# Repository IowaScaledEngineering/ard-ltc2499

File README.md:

# Iowa Scaled Engineering ARD-LTC2499

## Summary

The [ARD-LTC2499](https://www.iascaled.com/store/ARD-LTC2499) is an Arduino-compatible shield that contains a Linear Technology LTC2499 24-bit ADC
coupled with an LT6654 precision voltage reference. It is capable of converting 16 single-ended channels,
8 differential channels, or any other combination. In addition to measuring voltage, the ADC can interface
directly to a variety of sensors including strain gauges, thermocouples, and current shunts. The onboard EEPROM
can be used to store calibration and configuration information directly on each ARD-LTC2499 board.
A 6-byte EUI-48-compatible globally unique ID number is also provided.  The ARD-LTC2499 can be used with other
Arduino shields to make a simple, yet very accurate, data acquisition system.

Note:  The normal ARD-LTC2499 is not compatible with Arduinos using 3.3V I/O on the I2C lines, such as the Due, Zero, etc.
This is because the LTC2499 requires a 5V supply to deal with the 4.096V reference voltage, making it incompatible with 3.3V I2C.
A 3.3V compatible version is [available as the ARD-LTC2499-3V3](https://www.iascaled.com/store/ARD-LTC2499-3V3), which
is identical except that it also includes on-board level shifters for the I2C lines.

### Features

* Precision 24-bit delta sigma ADC in an Arduino-friendly form factor
* 16 single-ended channels, 8 differential channels, or any combination
* 7.5 samples/sec (or 15 samples/second without automatic offset cancellation)
* Input common mode voltage range of -0.3V to 5.3V
* Input measurement range of 0-2.048V (single-ended) or -2.048V to 2.048V (differential)
* 4.096V LT6654 precision voltage reference on board
* Optional onboard 5V linear regulator provides clean power to the ADC and reference
* 128 bytes of onboard EEPROM for storing configuration or calibration values
* Read-only 6-byte EUI-48-compatible globally unique ID
* Arduino software library for easy use
* 5V compatible I2C interface (or 3.3-5V with the ARD-LTC2499-3V3)

## Operation of the ARD-LTC2499 Hardware

The latest schematics for both the ARD-LTC2499 and the ARD-LTC2499-3V3 can be found here:
* [ARD-LTC2499 v1.3](https://github.com/IowaScaledEngineering/ard-ltc2499/raw/master/pg/ard-ltc2499-v1.3-83eb2df/ard-ltc2499.pdf)
* [ARD-LTC2499-3V3 v1.3](https://github.com/IowaScaledEngineering/ard-ltc2499/raw/master/pg/ard-ltc2499-v1.3LS-ffd4822/ard-ltc2499.pdf)

The Golden Rule:  When in doubt, check [the LTC2499
datasheet](https://www.analog.com/media/en/technical-documentation/data-sheets/2499fe.pdf).  This guide is not
designed to be a comprehensive guide to the LTC2499.

The useful measuring range of the inputs is 0V to 2.048V in single-ended mode, and a +/-2.048V in differential mode.
Be careful of common mode limits, however. Inputs have an absolute maximum common mode limit of -0.3V to +0.3V above VCC (nominally 5V)
before damage to the part will occur, so while the differential inputs can have -2.048V between them, neither side of the input may
violate the limit of -0.3V to 5.3V without damaging the part.

To eliminate any possibility of introducing gain or offset errors from buffering, the pins of the LTC2499 are brought directly
to the terminal headers. Please be careful when handling and using the board. Errant electrostatic discharge or voltages applied
outside the absolute maximum limits specified in the datasheet can cause immediate damage.

The 4.096V Reference output on J3 comes directly from the LT6654 reference output with no buffering. The LT6654 is rated for a
maximum of +/- 10mA. Also note that any current drawn from this pin will degrade the accuracy of the reference by a
small amount (see the Electrical Characteristics table, "Load Regulation", in the LT6654 datasheet).

### Hardware Configuration

In order to adapt to a wide variety of use cases and ArduinoTM configurations, the ARD-LTC2499 board has a number of configuration jumpers.

* JP1 - I2C Pull-up Enable
* JP2 - I2C Pin Selection
* JP3 - Onboard 5V Linear Regulator Enable
* JP4, JP5 & JP6 - LTC2499 I2C Address
* JP7 & JP8 - EEPROM I2C Address

_JP1 - I2C Pull-up Enable_

The I2C bus depends upon a set of pull-up resistors to function correctly. Each I2C bus should have one and only one set of
pull-ups enabled. The ARD-LTC2499 includes a set of 1.6k pull-up resistors that can be enabled by jumpering pins 1-2 and pins 3-4 of JP1.
Note that Arduino boards do not typically provide I2C pull-ups, so at least one board connected to I2C must provide them.

_JP2 - I2C Pin Selection_

Not all Arduinos provide I2C on the same pins. With the Rev 3 hardware designs (almost all of them as of 2021), there are now a
dedicated set of pins above AREF and GND marked "SDA" and "SCL". If you see those on your board, then place jumpers between
pins 3-5 and 4-6 on JP2 to connect the I2C bus to them.

If you board does not have explicit SDA and SCL pins, then most likely they're shared with pins A4 and A5. Place jumpers
between pins 1-3 and 2-4 to select those instead.

_JP3 - Onboard 5V Linear Regulator Enable_

To free the LTC2499 from any noise on the Arduino's 5V supply caused by the AVR or other shields, the ARD-LTC2499 includes an
onboard 78L05 regulator coming from the Arduino's "VIN" pin. If you are powering the Arduino with >8VDC via the power jack,
you can use the ARD-LTC2499 onboard 5V regulator to provide nice quiet power by jumpering pins 3-4 of JP3.

If you are powering the Arduino off of the 5V provided by USB or via some other means that does not place >8VDC on the VIN pin,
then the regulator will not work and must not be used. JP3 must be placed between pins 1-2 in this case.

_JP4, JP5 & JP6 - LTC2499 I2C Address_

Each device on the I2C bus must have a unique device address. The LTC2499 has 27 possible addresses depending on how
JP4, JP5, and JP6 are set. Each may be set high (jumpering pins 1-2, the two closest to the LTC2499), low (jumpering pins 3-4,
the ones furthest from the 2499) or floating (no jumpered pins or pins 2-3 jumpered).  JP4 corresponds to CA0, JP5 to CA1, and JP6 to CA2 on the LTC2499.

| JP4    | JP5    | JP6    | 7-bit I2C Address | Ard2499 Define       |
|--------|--------|--------|-------------------|----------------------|
| Low    | Low    | Low    | 0x14              | ARD2499_ADC_ADDR_000 |
| Low    | Low    | Open   | 0x15              | ARD2499_ADC_ADDR_00Z |
| Low    | Low    | High   | 0x16              | ARD2499_ADC_ADDR_001 |
| Low    | Open   | Low    | 0x17              | ARD2499_ADC_ADDR_0Z0 |
| Low    | Open   | Open   | 0x24              | ARD2499_ADC_ADDR_0ZZ |
| Low    | Open   | High   | 0x25              | ARD2499_ADC_ADDR_0Z1 |
| Low    | High   | Low    | 0x26              | ARD2499_ADC_ADDR_010 |
| Low    | High   | Open   | 0x27              | ARD2499_ADC_ADDR_01Z |
| Low    | High   | High   | 0x28              | ARD2499_ADC_ADDR_011 |
| Open   | Low    | Low    | 0x35              | ARD2499_ADC_ADDR_Z00 |
| Open   | Low    | Open   | 0x36              | ARD2499_ADC_ADDR_Z0Z |
| Open   | Low    | High   | 0x37              | ARD2499_ADC_ADDR_Z01 |
| Open   | Open   | Low    | 0x44              | ARD2499_ADC_ADDR_ZZ0 |
| Open   | Open   | Open   | 0x45              | ARD2499_ADC_ADDR_ZZZ |
| Open   | Open   | High   | 0x46              | ARD2499_ADC_ADDR_ZZ1 |
| Open   | High   | Low    | 0x47              | ARD2499_ADC_ADDR_Z10 |
| Open   | High   | Open   | 0x54              | ARD2499_ADC_ADDR_Z1Z |
| Open   | High   | High   | 0x55              | ARD2499_ADC_ADDR_Z11 |
| High   | Low    | Low    | 0x56              | ARD2499_ADC_ADDR_100 |
| High   | Low    | Open   | 0x57              | ARD2499_ADC_ADDR_10Z |
| High   | Low    | High   | 0x64              | ARD2499_ADC_ADDR_101 |
| High   | Open   | Low    | 0x65              | ARD2499_ADC_ADDR_1Z0 |
| High   | Open   | Open   | 0x66              | ARD2499_ADC_ADDR_1ZZ |
| High   | Open   | High   | 0x67              | ARD2499_ADC_ADDR_1Z1 |
| High   | High   | Low    | 0x74              | ARD2499_ADC_ADDR_110 |
| High   | High   | Open   | 0x75              | ARD2499_ADC_ADDR_11Z |
| High   | High   | High   | 0x76              | ARD2499_ADC_ADDR_111 |

_JP7 & JP8 - EEPROM I2C Address_

Each device on the I2C bus must have a unique device address. The 24AA025E48 EEPROM that provides both non-volatile storage
and the globally unique ID number has four possible addresses depending on how JP7 and JP8 are set. Each may be set high (no jumper)
or low (jumper in place). Please refer to the Figure 5-2 in the 24AA025E48 datasheet (we use the SOT-23 version, so A2 is always '0' -
otherwise JP8 is A1 and JP7 is A0) or the Ard2499 library header for corresponding address values.

| JP7    | JP8    | 7-bit I2C Address | Ard2499 Define      |
|--------|--------|-------------------|---------------------|
| Jumper | Jumper | 0x50              | ARD2499_EEP_ADDR_00 |
| Jumper | Open   | 0x51              | ARD2499_EEP_ADDR_0Z |
| Open   | Jumper | 0x52              | ARD2499_EEP_ADDR_Z0 |
| Open   | Open   | 0x53              | ARD2499_EEP_ADDR_ZZ |

## Ard2499 Arduino Software Library

### Introduction

The Ard2499 library was designed to make the Iowa Scaled Engineering ARD-LTC2499 shield easy to use with the Arduino environment.
The board itself is provides a breakout for the Linear Technology LTC2499 24-bit 8/16 channel delta-sigma ADC, adding other useful
features like a precision 4.096V LT6654 reference, 128 bytes of onboard EEPROM for storing configuration or calibration values,
and a read-only 6-byte EUI48-compatible globally unique ID number.

Note:  The software library is now maintained in [its own repository](https://github.com/IowaScaledEngineering/arduino-ard2499) for compatibility
with Arduino's Library Manager.

### Setup

There are two ways to install the Ard2499 library in the Arduino environment.

The easiest way is through Arduino's Library Manager.  You should be able to search for Ard2499 and have the library available for installation shortly.
We're working on it.

Alternately, you can [download the zip file](https://github.com/IowaScaledEngineering/arduino-ard2499/archive/main.zip) from the
IowaScaledEngineering/arduino-ard2499 project on Github and follow the ["Importing a .zip Library" instructions](https://www.arduino.cc/en/guide/libraries#toc4).

### Example Sketch

Once the library is installed, you should see Ard2499 under File->Examples in your Arduino environment.  A sample Arduino sketch that demonstrates some
simple uses of the library is available as ard2499_example directory.

### Library Usage Details

The core of the Ard2499 library is the Ard2499 object.  One instance should be instantiated for each ARD-LTC2499 board that you are using.

When an instance is created, an optional TwoWire object can be passed to the constructor.  Otherwise, the Ard2499 library assumes that the board will be communicating using the Wire object.

#### Functional Interface

```byte Ard2499::begin(byte ltc2499Address, byte eepromAddress, uint16_t referenceMillivolts = 4096);```

The Ard2499::begin() function should be called within the setup() function of your sketch. It requires the 7-bit address of both the LTC2499 and EEPROM on the ARD-LTC2499 to initialize both parts.
The addresses can be passed in directly as a number, or by using the address macros.  By using different addresses, it's possible to stack ARD-LTC2499 boards and have a different object to control each one.

An optional reference voltage, in millivolts, can be passed if the ARD-LTC2499 has a non-standard reference on board. If not specified, it defaults to 4096mV, which is the voltage
for any non-special order board.

Returns:  Ard2499::begin() will return a byte corresponding to a bitmast of errors, with 0 corresponding to complete success.
* ARD2499_SUCCESS (0x00) upon both devices being initialized successfully
* ARD2499_LTC2499_ERR (0x01) if the LTC2499 is not initialized successfully
* ARD2499_EEPROM_ERR (0x02) if the EEPROM is not initialized successfully

```byte Ard2499::ltc2499ChangeChannel(byte channel)```

The Ard2499::ltc2499ChangeChannel() function will wait for up to 200 milliseconds for the LTC2499 to become available, change the LTC2499's input multiplexer to the channel
specified in channel and start a new conversion. The value in channel corresponds to the lower 5 bits in the first configuration word of the device. In addition to computing
values for channel yourself, you can use the channel macros.

Additionally, channel can be configured to LTC2499_CHAN_TEMPERATURE to return the LTC2499 internal temperature. While the temperature input isn't a "channel" on the multiplexer,
the library makes it appear this way.

Returns:
* ARD2499_SUCCESS (0x00) if the channel change completed
* ARD2499_LTC2499_ERR (0x02) if the channel change failed

```byte Ard2499::ltc2499ChangeConfiguration(byte config)```

The Ard2499::ltc2499ChangeConfiguration() function will wait for up to 200 milliseconds for the LTC2499 to become available, change the LTC2499's configuration to that
specified in config and start a new conversion. The value in config corresponds to bits 3-5 in the second configuration word of the device. In addition to computing values
for config yourself, you can use the configuration macros.

Returns:
* ARD2499_SUCCESS (0x00) if the configuration change completed
* ARD2499_LTC2499_ERR (0x02) if the configuration change failed

```long Ard2499:: ltc2499Read()```

The Ard2499::ltc2499Read() function will wait for up to 200 milliseconds for the LTC2499 to become available, read the last conversion value, start a new conversion,
and clean up the conversion result.

Returns:
* -16777216 to +16777215 - normal conversion result
* LTC2499_READ_ERROR (0x01000001) if the read timed out or otherwise failed
* LTC2499_OVERRANGE_POSITIVE (0x01000000) if (IN+ - IN-) > 2.048V
* LTC2499_OVERRANGE_NEGATIVE (0x11000000) if (IN+ - IN-) < 2.048V

```long Ard2499:: ltc2499ReadAndChangeChannel(byte nextChannel)```

The Ard2499::ltc2499ReadAndChangeChannel() function will first attempt to change the input multiplexer channel and then perform a read. This is useful for not wasting
the conversion (and delay) resulting from a normal Ard2499::ltc2499Read() if the next operation is just going to be changing the input channel. Note: the channel change
does not take effect until after the data is read - in other words, for the next conversion.

Channel change behaviour works exactly like Ard2499::ltc2499ChangeChannel(). In the event that the channel change fails, LTC2499_READ_ERROR will be returned. Otherwise,
read and return behaviour works exactly like Ard2499::ltc2499Read().

```unsigned long Ard2499:: ltc2499ReadRaw()```

The Ard2499::ltc2499ReadRaw() function will wait for up to 200 milliseconds for the LTC2499 to become available, read the last conversion value, start a new conversion,
and return the native 32 bit conversion result. The lowest 6 bits will be "sub-LSB" bits, and the highest bit will be what the datasheet designates "SIG". This is for
advanced users who want direct access to the conversion result.

Returns:
* LTC2499_RAW_READ_ERROR (0xFFFFFFFF) if the read timed out or otherwise failed
* Any other result is a direct read from the LTC2499

```unsigned long Ard2499:: ltc2499ReadRawAndChangeChannel(byte nextChannel)```

The Ard2499::ltc2499ReadRawAndChangeChannel() function will first attempt to change the input multiplexer channel and then perform a raw read. This is useful for
not wasting the conversion (and delay) resulting from a normal Ard2499::ltc2499ReadRaw() if the next operation is just going to be changing the input channel.
Note: the channel change does not take effect until after the data is read - in other words, for the next conversion. The raw read capability is for advanced
users who want direct access to the conversion result.

Channel change behaviour works exactly like Ard2499::ltc2499ChangeChannel(). In the event that the channel change fails, LTC2499_RAW_READ_ERROR will be returned.
Otherwise, read and return behaviour works exactly like Ard2499:: ltc2499ReadRaw().

```unsigned int Ard2499:: ltc2499ReadTemperatureDeciK()```

The Ard2499::ltc2499ReadTemperatureDeciK() function will check if the current channel is LTC2499_CHAN_TEMPERATURE and if not, wait up to 200 milliseconds for
converter availability, change it and start a new conversion. It will then wait for up to 200 milliseconds for the LTC2499 to complete the conversion and turn it
into a unsigned int corresponding to the LTC2499's current temperature in 1/10th degrees Kelvin.

Upon failure, it will return zero, as hopefully no project you're working on is operating at absolute zero. If it is and the part still seems to be working
otherwise, call us and we'll help you write the paper for your physics journal of choice.

```float ltc2499ReadTemperature(byte temperatureUnits)```

The Ard2499::ltc2499ReadTemperature() function will check if the current channel is LTC2499_CHAN_TEMPERATURE and if not, wait up to 200 milliseconds for converter
availability, change it and start a new conversion. It will then wait for up to 200 milliseconds for the LTC2499 to complete the conversion and turn it into single
precision floating point value corresponding to the LTC2499's current temperature in the units specified in temperatureUnits.

Upon failure, it will return zero.

The value of temperatureUnits should be ARD2499_TEMP_K (degrees Kelvin), ARD2499_TEMP_C (degrees Celsius), or ARD2499_TEMP_F (degrees Fahrenheit).

Note: Because this function uses floating point on an 8 bit processor without any sort of hardware floating point support, expect performance to be abysmal on
AVR-based Arduinos. But it's handy if you don't care about performance.

```const char* Ard2499::eui48Get()```

The Ard2499::eui48Get() function will retrieve the board's 48-bit, globally unique, EUI-48TM-compatible identification number as a string.

Returns:

Ard2499::eui48Get() will return a character pointer to a constant, NULL-terminated string. The value will be either 12 characters of hexadecimal number,
or "Unknown" if the Ard2499::begin() failed to find the EEPROM. (Ard2499::begin() would have returned a value with the ARD2499_EEPROM_ERR bit set.)

```byte Ard2499::eepromRead(int address, byte defaultOnError=0x00)```

The Ard2499::eepromRead() function will retrieve a byte from the ARD-LTC2499's onboard EEPROM at the location specified by address. Valid values for address are 0x00-0x7F.

Optionally, the function can take a second argument - defaultOnError - of the value to be returned if the EEPROM is not initialized or is not accessible when the function
is called. If the defaultOnError parameter is omitted, it will default to returning 0x00 on failure.

```byte Ard2499::eepromWrite(int address, byte value, byte blocking=1)```

The Ard2499::eepromWrite() function will write a byte of value value to the ARD-LTC2499's onboard EEPROM at the location specified by address. Valid values for address are
0x00-0x7F, and value can be 0x00-0xFF.

Optionally, the function can take a third argument - blocking. The Microchip 24AA025E48 EEPROM used on the ARD-LTC2499 can take up to 5 milliseconds to actually commit
a write to EEPROM. If blocking is non-zero or omitted, the eepromWrite() function will block until it can confirm that the write is completed or until it times out
after 10 millseconds.

Note that blocking will not cause the value to be verified - it merely causes the function to block until the part begins acknowledging I2C/TWI transactions once
again, indicating that the write cycle is complete.

Returns:
* ARD2499_SUCCESS (0x00) if the write completed
* ARD2499_EEPROM_ERR (0x02) if the write failed

#### LTC2499 Address Defines

The address for the LTC2499 is configurable on the ARD-LTC2499 using jumpers JP4-JP6. You can either use the datasheet and directly enter the LTC2499's address into
the Ard2499::begin() function, or use some convenient macros.

The macros are all in the form of ARD2499_ADC_ADDR_cba, where a, b, and c can take on the value of '0', '1', or 'Z'. Placeholder 'a' represents jumper JP4, 'b' represents JP5,
and 'c' JP6. '0' indicates that the center pin is jumpered to the low pins (towards inputs 8-15 on the board), '1' indicates that it is jumpered to the high pins
(towards the LTC2499 or inputs 0-7), and 'Z' indicates that it's left floating (no jumpers or jumper across pin 2-3).

So, if all three were left open, you'd use ARD2499_ADC_ADDR_ZZZ. Likewise, for JP4 to bottom, JP5 to top, and JP6 open you'd use ARD2499_ADC_ADDR_Z10.

#### EEPROM Address Defines

The address for the EEPROM is configurable on the ARD-LTC2499 using jumpers JP7-JP8. You can either use the datasheet and directly enter the 24AA025E48's address into the
Ard2499::begin() function, or use some convenient macros.

The macros are all in the form of ARD2499_EEP_ADDR_ba, where a and b can take on the value of '0' or 'Z'. Placeholder 'a' represents jumper JP7 and 'b' represents JP8.
'0' indicates that a jumper has been placed across those pins, and 'Z' indicates that it's left floating (no jumper).

So, if both were left open, you'd use ARD2499_EEP_ADDR_ZZ. Likewise, for JP7 jumpered and JP8 open ARD2499_EEP_ADDR_Z0.

#### Channel Defines

The library provides definitions of all the common channel combinations to allow the easy selection of input channels without knowing all the internal LTC2499 bits to set.

Differential configurations take the form LTC2499_CHAN_DIFF_aP_bN, where 'a' represents the channel number of the positive input (IN+ in the LTC2499 datasheet)
and 'b' represents the channel number of the negative input (IN-).

Single-ended configurations are in the form LTC2499_CHAN_SINGLE_aP, where again 'a' represents the channel number of the positive (IN+) input.

Additionally, the internal temperature sensor can be selected by using LTC2499_CHAN_TEMPERATURE.

Some examples:
* LTC2499_CHAN_DIFF_2P_3N - Differential, input 2 is IN+, input 3 is IN-
* LTC2499_CHAN_DIFF_11P_10N - Differential, input 11 is IN+, input 10 is IN-
* LTC2499_CHAN_SINGLE_2P - Single ended, input 2 as IN+
* LTC2499_CHAN_SINGLE_10P - Single ended, input 10 as IN+
* LTC2499_CHAN_TEMPERATURE - Connect to internal temperature sensor.

#### Configuration Macros

Bit position macros are provided corresponding to the bits used to define the LTC2499 configuration in the second configuration byte:
* LTC2499_CONFIG2_FA
* LTC2499_CONFIG2_FB
* LTC2499_CONFIG2_SPD

These can be combined into a configuration value by an expression such as:

(_BV(LTC2499_CONFIG2_FA) | _BV(LTC2499_CONFIG2_SPD))

Please see the LTC2499 datasheet, Table 4, to see how these are used directly.

Additionally, the library has some convenient combinations:
* LTC2499_CONFIG2_50HZ_REJ - Reject at 50Hz
* LTC2499_CONFIG2_60HZ_REJ - Reject at 60Hz
* LTC2499_CONFIG2_60_50HZ_REJ - Reject at both 50/60Hz
* LTC2499_CONFIG2_SPEED_2X - Set for double speed conversions, drop offset calibration (15 samples/sec)

To use these, pick one of the rejection configurations and - optionally - bitwise or it with the double speed option and pass it to the the ltc2499ChangeConfiguration() function. For example:

```retval = ard2499.ltc2499ChangeConfiguration(LTC2499_CONFIG2_60_50HZ_REJ | LTC2499_CONFIG2_SPEED_2X)```

### A Note About Converter Latency

Important! Note that the LTC2499 will start a conversion whenever it is read (using ltc2499Read() or similar) or whenever the channel
or configuration is changed. Each conversion will take ~133 milliseconds in 1X mode and ~67 milliseconds in 2X mode. During this conversion time,
the LTC2499 will not respond to I2C/TWI requests. Thus, all calls interacting with the LTC2499 implement code to block until a sane timeout is
reached or the part starts responding. Be aware that when you use these functions, your code may hang up for a conversion time.

To minimize the wasted conversions, functions that read the current value and immediately change the channel (without wasting an entire
conversion cycle in between) are provided in addition to the standard read and channel change functions.

### Source Releases

The latest source code is always available from our GitHub [arduino-ard2499 repository](https://github.com/IowaScaledEngineering/arduino-ard2499).  We've broken it out
from the [main hardware project](https://github.com/IowaScaledEngineering/ard-ltc2499) to allow it to be included into Arduino's Library Manager automatically.

## Open Hardware & Software

Like all public Iowa Scaled Engineering designs, the ARD-LTC2499 is both open hardware and open source software.  The hardware is licensed under Creative Commons BY-SA, and the software is GPL v3.

The board was designed using the gEDA suite of tools (gschem, pcb, etc.), and the files are in the sch, sym, and pcb subdirectories.

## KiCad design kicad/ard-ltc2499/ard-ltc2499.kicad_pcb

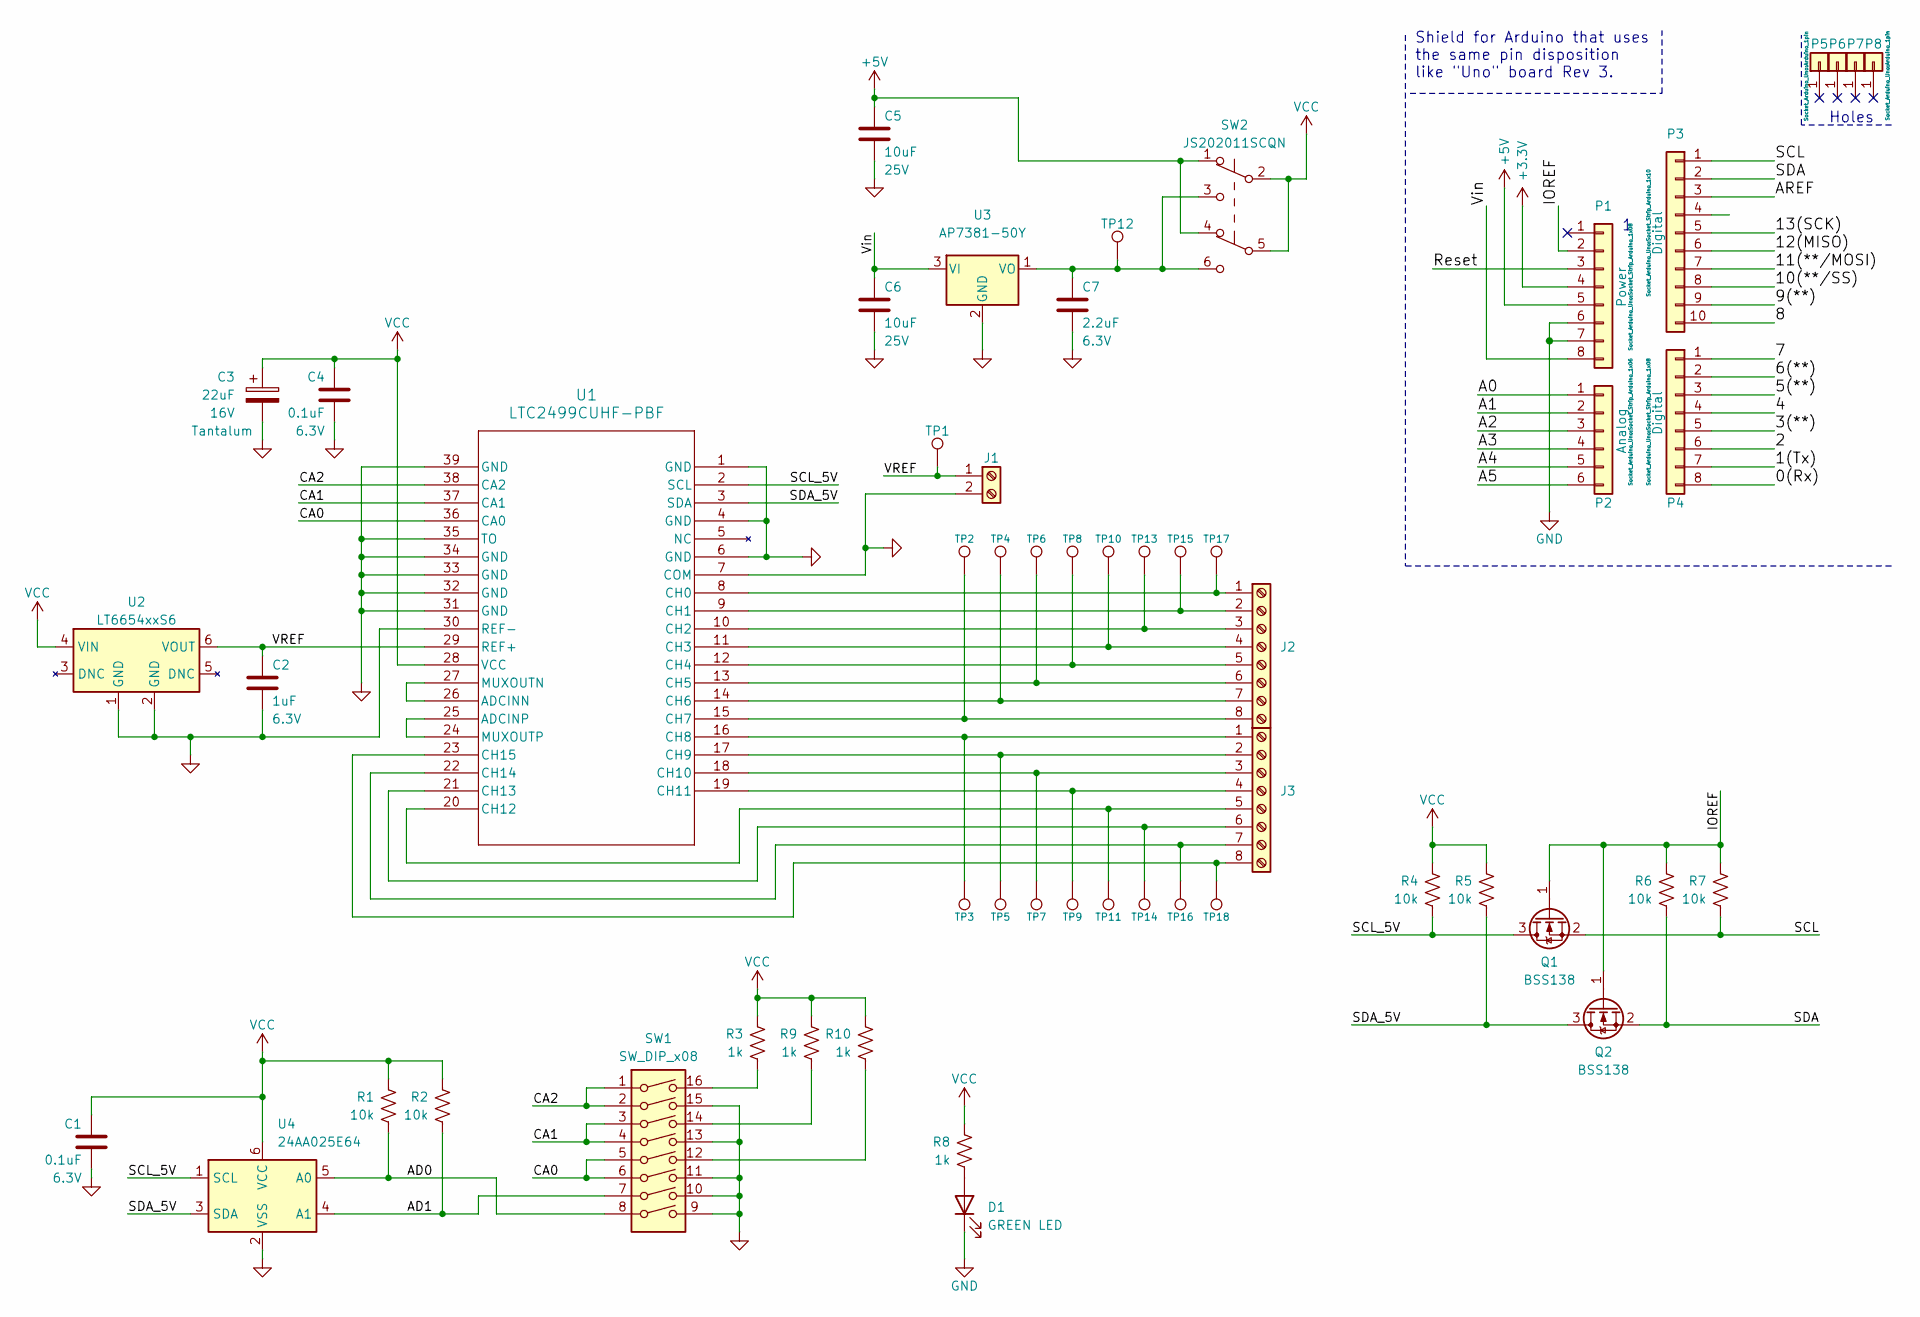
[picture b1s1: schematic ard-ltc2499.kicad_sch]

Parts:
C1, C4: 0.1uF; C_0805_2012Metric; Voltage 6.3V
C2: 1uF; C_0805_2012Metric; Voltage 6.3V
C3: 22uF; CP_EIA-3216-18_Kemet-A; Voltage 16V
C5, C6: 10uF; C_0805_2012Metric; Voltage 25V
C7: 2.2uF; C_0805_2012Metric; Voltage 6.3V
D1: GREEN LED; LED_0805_2012Metric
J1: Screw_Terminal_01x02; TerminalBlock_RND_205-00012_1x02_P5.00mm_Horizontal
J2, J3: Screw_Terminal_01x08; TerminalBlock_TE_282834-8_1x08_P2.54mm_Horizontal
P1: Power; Socket_Strip_Arduino_1x08
P2: Analog; Socket_Strip_Arduino_1x06
P3: Digital; Socket_Strip_Arduino_1x10
P4: Digital; Socket_Strip_Arduino_1x08
P5, P6, P7, P8: CONN_01X01; Arduino_1pin
Q1, Q2: BSS138; SOT-23
R1, R2, R4, R5, R6, R7: 10k; R_0805_2012Metric
R3, R8, R9, R10: 1k; R_0805_2012Metric
SW1: SW_DIP_x08; SW_DIP_SPSTx08_Slide_6.7x21.88mm_W8.61mm_P2.54mm_LowProfile
SW2: JS202011SCQN; SW_JS202011SCQN
TP1, TP2, TP3, TP4, TP5, TP6, TP7, TP8, TP9, TP10, TP11, TP12, TP13, TP14, TP15, TP16, TP17, TP18: TestPoint; TestPoint_Pad_D1.5mm
U1: LTC2499CUHF-PBF; QFN-38_UHF_LIT
U2: LT6654xxS6; TSOT-23-6
U3: AP7381-50Y; SOT-89-3
U4: 24AA025E64; TSOT-23-6

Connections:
+3V3: P1.4
+5V: C5.1, P1.5, SW2.1 (A), SW2.4 (A)
/0(Rx): P4.8
/1(Tx): P4.7
/2: P4.6
/3(**): P4.5
/4: P4.4
/5(**): P4.3
/6(**): P4.2
/7: P4.1
/8: P3.10
/9(**): P3.9
/10(**/SS): P3.8
/11(**/MOSI): P3.7
/12(MISO): P3.6
/13(SCK): P3.5
/A0: P2.1
/A1: P2.2
/A2: P2.3
/A3: P2.4
/A4: P2.5
/A5: P2.6
/AD0: R1.1, SW1.8, U4.5 (A0)
/AD1: R2.1, SW1.7, U4.4 (A1)
/AREF: P3.3
/CA0: SW1.5, SW1.6, U1.36 (CA0)
/CA1: SW1.3, SW1.4, U1.37 (CA1)
/CA2: SW1.1, SW1.2, U1.38 (CA2)
/IOREF: P1.2, Q1.1 (G), Q2.1 (G), R6.2, R7.2
/Reset: P1.3
/SCL: P3.1, Q1.2 (S), R7.1
/SCL_5V: Q1.3 (D), R4.1, U1.2 (SCL), U4.1 (SCL)
/SDA: P3.2, Q2.2 (S), R6.1
/SDA_5V: Q2.3 (D), R5.1, U1.3 (SDA), U4.3 (SDA)
/VREF: C2.1, J1.1, TP1.1, U1.29 (REF+), U2.6 (VOUT)
/Vin: C6.1, P1.8, U3.3 (VI)
GND: C1.2, C2.2, C3.2, C4.2, C5.2, C6.2, C7.2, D1.1 (K), J1.2, P1.6, P1.7, SW1.9, SW1.10, SW1.11, SW1.13, SW1.15, U1.1 (GND), U1.4 (GND), U1.6 (GND), U1.7 (COM), U1.30 (REF-), U1.31 (GND), U1.32 (GND), U1.33 (GND), U1.34 (GND), U1.35 (TO), U1.39 (GND), U2.1 (GND), U2.2 (GND), U3.2 (GND), U4.2 (VSS)
unnamed: C7.1, SW2.3 (C), SW2.6 (C), TP12.1, U3.1 (VO)
unnamed: D1.2 (A), R8.1
unnamed: J2.1, TP17.1, U1.8 (CH0)
unnamed: J2.2, TP15.1, U1.9 (CH1)
unnamed: J2.3, TP13.1, U1.10 (CH2)
unnamed: J2.4, TP10.1, U1.11 (CH3)
unnamed: J2.5, TP8.1, U1.12 (CH4)
unnamed: J2.6, TP6.1, U1.13 (CH5)
unnamed: J2.7, TP4.1, U1.14 (CH6)
unnamed: J2.8, TP2.1, U1.15 (CH7)
unnamed: J3.1, TP3.1, U1.16 (CH8)
unnamed: J3.2, TP5.1, U1.17 (CH9)
unnamed: J3.3, TP7.1, U1.18 (CH10)
unnamed: J3.4, TP9.1, U1.19 (CH11)
unnamed: J3.5, TP11.1, U1.20 (CH12)
unnamed: J3.6, TP14.1, U1.21 (CH13)
unnamed: J3.7, TP16.1, U1.22 (CH14)
unnamed: J3.8, TP18.1, U1.23 (CH15)
unnamed: R3.1, SW1.16
unnamed: R9.1, SW1.14
unnamed: R10.1, SW1.12
unnamed: U1.24 (MUXOUTP), U1.25 (ADCINP)
unnamed: U1.26 (ADCINN), U1.27 (MUXOUTN)
VCC: C1.1, C3.1, C4.1, R1.2, R2.2, R3.2, R4.2, R5.2, R8.2, R9.2, R10.2, SW2.2 (B), SW2.5 (B), U1.28 (VCC), U2.4 (VIN), U4.6 (VCC)

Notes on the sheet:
Holes
Shield for Arduino that uses the same pin disposition like "Uno" board Rev 3.

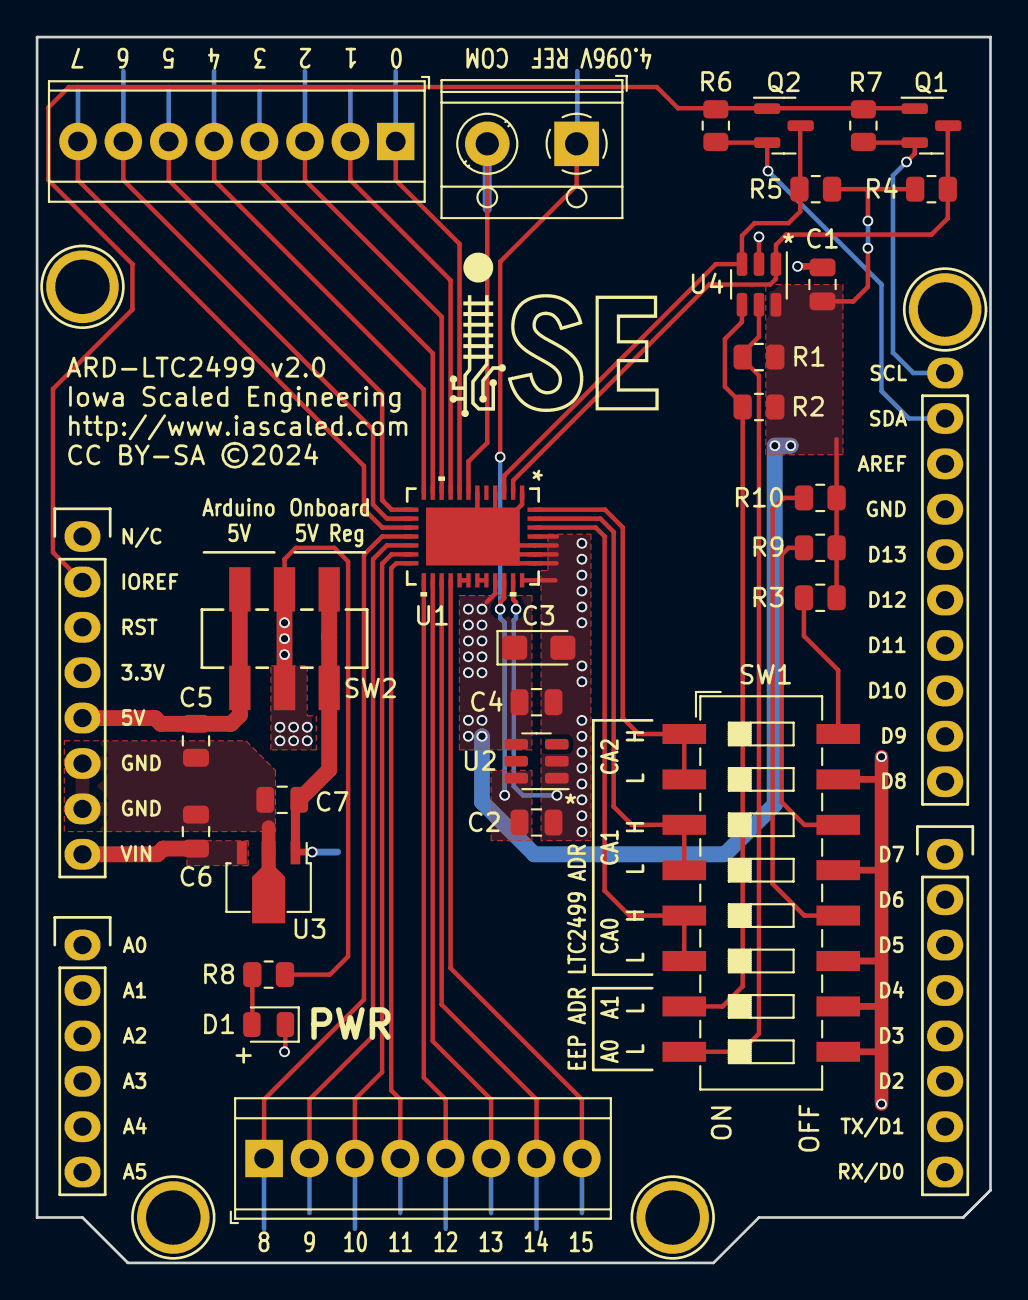
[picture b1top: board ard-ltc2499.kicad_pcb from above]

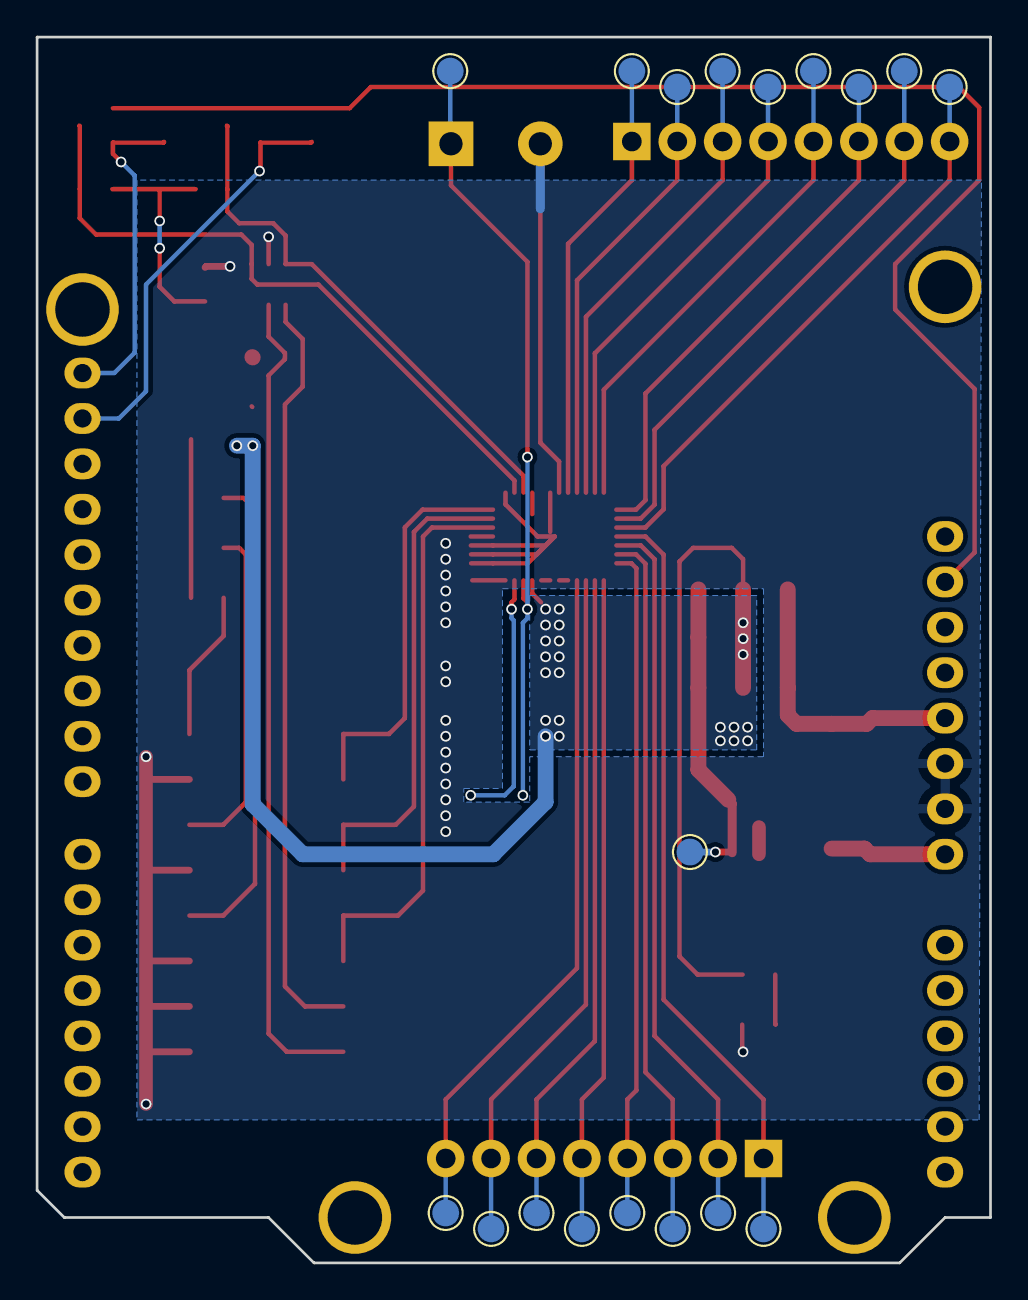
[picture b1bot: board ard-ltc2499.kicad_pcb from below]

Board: 2 copper layers, 53.3 x 68.6 mm, 55 parts (18 on the bottom side), 38 nets.

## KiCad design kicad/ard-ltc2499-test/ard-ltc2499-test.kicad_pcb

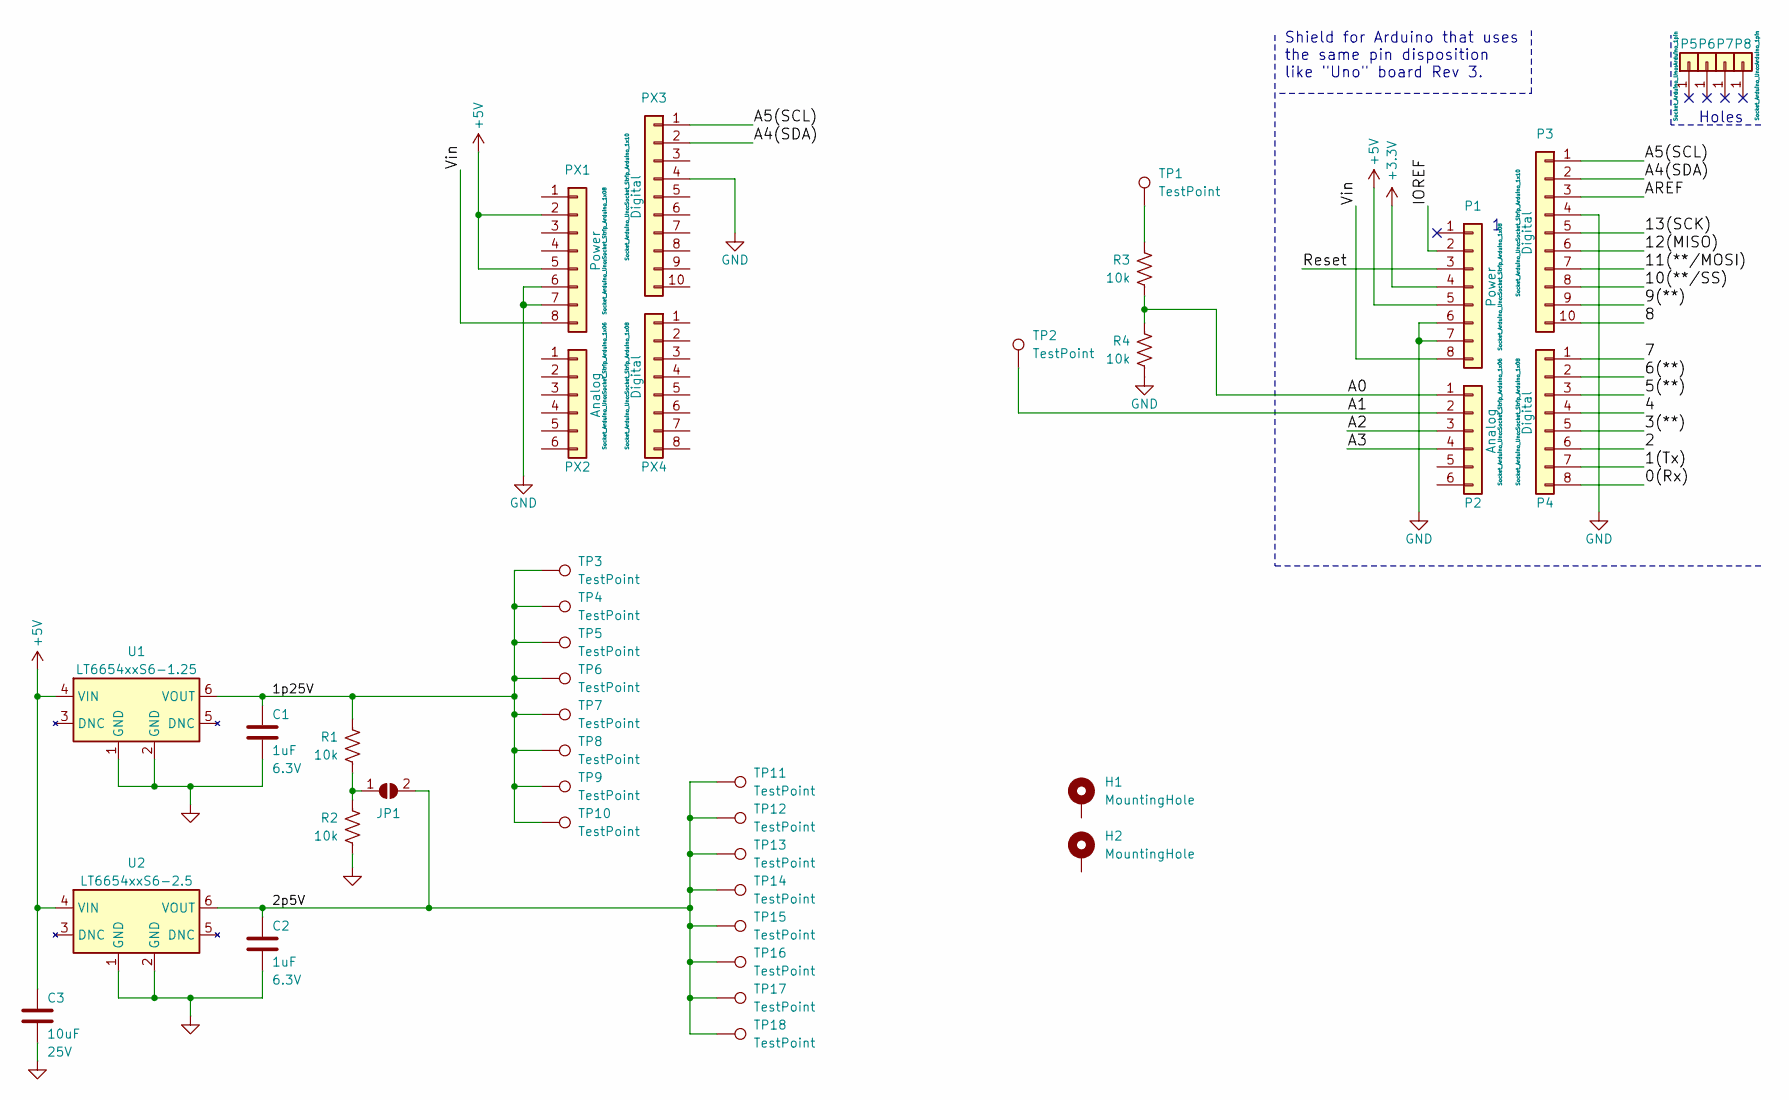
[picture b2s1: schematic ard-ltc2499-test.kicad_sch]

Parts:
C1, C2: 1uF; C_0805_2012Metric; Voltage 6.3V
C3: 10uF; C_0805_2012Metric; Voltage 25V
H1, H2: MountingHole; MountingHole_3.2mm_M3_Pad
JP1: SolderJumper_2_Open; SolderJumper-2_P1.3mm_Open_RoundedPad1.0x1.5mm
P1: Power; Socket_Strip_Arduino_1x08
P2: Analog; Socket_Strip_Arduino_1x06
P3: Digital; Socket_Strip_Arduino_1x10
P4: Digital; Socket_Strip_Arduino_1x08
P5, P6, P7, P8: CONN_01X01; Arduino_1pin
PX1: Power; Socket_Strip_Arduino_1x08
PX2: Analog; Socket_Strip_Arduino_1x06
PX3: Digital; Socket_Strip_Arduino_1x10
PX4: Digital; Socket_Strip_Arduino_1x08
R1, R2, R3, R4: 10k; R_0805_2012Metric
TP1, TP2, TP3, TP4, TP5, TP6, TP7, TP8, TP9, TP10, TP11, TP12, TP13, TP14, TP15, TP16, TP17, TP18: TestPoint; PinHeader_1x01_P2.54mm_Vertical
U1: LT6654xxS6-1.25; TSOT-23-6
U2: LT6654xxS6-2.5; TSOT-23-6

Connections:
+3V3: P1.4
+5V: C3.1, P1.5, PX1.2, PX1.5, U1.4 (VIN), U2.4 (VIN)
/0(Rx): P4.8
/1(Tx): P4.7
/1p25V: C1.1, R1.2, TP3.1, TP4.1, TP5.1, TP6.1, TP7.1, TP8.1, TP9.1, TP10.1, U1.6 (VOUT)
/2: P4.6
/2p5V: C2.1, JP1.2 (B), TP11.1, TP12.1, TP13.1, TP14.1, TP15.1, TP16.1, TP17.1, TP18.1, U2.6 (VOUT)
/3(**): P4.5
/4: P4.4
/5(**): P4.3
/6(**): P4.2
/7: P4.1
/8: P3.10
/9(**): P3.9
/10(**/SS): P3.8
/11(**/MOSI): P3.7
/12(MISO): P3.6
/13(SCK): P3.5
/A0: P2.1, R3.1, R4.2
/A1: P2.2, TP2.1
/A2: P2.3
/A3: P2.4
/A4(SDA): P3.2, PX3.2
/A5(SCL): P3.1, PX3.1
/AREF: P3.3
/IOREF: P1.2
/Reset: P1.3
/Vin: P1.8, PX1.8
GND: C1.2, C2.2, C3.2, P1.6, P1.7, P3.4, PX1.6, PX1.7, PX3.4, R2.1, R4.1, U1.1 (GND), U1.2 (GND), U2.1 (GND), U2.2 (GND)
unnamed: JP1.1 (A), R1.1, R2.2
unnamed: R3.2, TP1.1

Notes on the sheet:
Holes
Shield for Arduino that uses the same pin disposition like "Uno" board Rev 3.

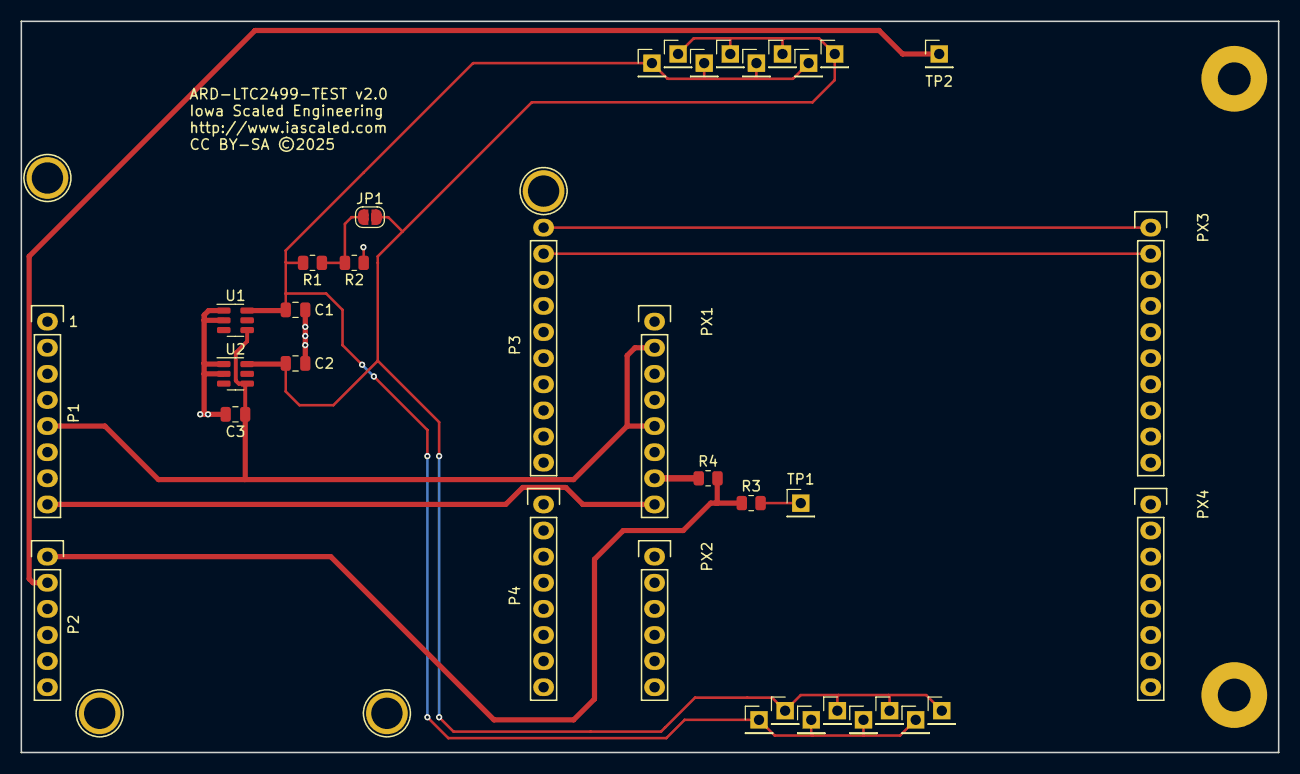
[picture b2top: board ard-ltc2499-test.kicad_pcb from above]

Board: 2 copper layers, 122.3 x 71.1 mm, 42 parts (0 on the bottom side), 11 nets.

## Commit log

2013-01-29 Initial checkin. PCB not complete.
2013-01-30 Finished PCB
2013-01-30 Small cleanup
2013-01-31 Changed C2 to polarized.
2013-01-31 More OCD
2013-01-31 Added polarized cap symbol.
2013-02-01 Added CC license.
2013-02-02 Connected COM to GND. LVS/DRC Clean.
2013-02-03 Add PG files.
2013-03-18 Initial bit of the 2499 arduino library
2013-03-26 This morning's work getting this dumb library to compile and at least eeprom functionality working
2013-03-26 Updates to "mostly working"-ish
2013-03-26 More misc fixes
2013-03-26 Example sketch starting point
2013-03-26 Rename directory to capitalize similar to other Arduino libraries
2013-03-26 Capitalization change
2013-03-27 Renamed the arduino example sketch Fixed a few bugs
2013-03-27 Fixes to add gplv3 boilerplate
2013-03-27 Forgot GPL stuff on arduino sketch
2013-05-02 Added relevant 2499 datasheets
2013-10-12 Added start for HV capable version
2013-10-12 Added thermocouple data
2013-11-25 Fixed LTC6654 to LT6654
2014-03-15 Examples
2014-03-19 Added alarm pin
2014-04-13 Update LTC2499 example code
2014-04-13 Make proper examples directory
2014-04-13 Move of example
2014-04-17 Moved examples to example directory
2014-04-22 Added power LED. Added pin1 marks to U1, U2, U4
2014-04-22 Changed rev to 1.1
2014-04-23 Cleaned up some schtuff.
2014-04-23 Added back silk
2014-04-23 OSHPark order
2014-04-25 Renamed to _reflow (was _thermocouple)
2014-04-27 Latest code with debug pins
2014-05-15 Updated example to enumerate the bus first. Cleaned up reflow example
2014-05-28 Changes to make it more widely arduino compatible
2014-05-28 Changes to example to better describe enumeration and add header text on sketch
2014-10-29 Added test program
2014-10-29 Added extra delay
2014-10-31 Modified to use 4-pin SMT jumpers
2014-10-31 Intermediate layout with SMT jumpers
2014-10-31 Final layout with SMT
2014-11-04 Silk changes to better explain jumpers
2014-11-04 Updated 2499 footprint (smaller paste hole). LVS/DRC clean.
2014-12-01 v1.2
2014-12-07 Fixed LTC2499_CONFIG2_CONFBITS - changed & to |
2014-12-28 Made channel check criteria a range, not just a single-ended comparison
2015-01-09 Create README.md
    Adding readme
2015-01-09 Add license files
2015-01-09 Update readme with more details about the board and ISE
2015-01-18 Modified channel test to check adjacent channel (looking for shorts)
2015-03-08 Verify still connected to original terminal after checking for adjacent.
2015-04-21 Reversed the positive and negative overrange codes in the library. Somehow these have been backwards for years and I've never noticed.
2015-04-24 Added wait for serial after opening port to improve behavior with Leonardo
2015-05-03 Initial commit of volt meter sketch
2015-05-24 Added voltage measurement at end.
2015-07-26 Added note for expected voltage
2015-11-12 Increased annulus around arduino headers (sch/pcb). Changed LED to 0805 (sch only). Changed 2x3 header to SMT (sch only). Replaced R1-R4 with rpack (sch only).
2015-11-12 PCB edits complete.
2015-11-12 Changed silk to 8mil
2015-11-25 New release for possible next production run
2016-01-21 Add ability to pass reference voltage in millivolts in the initializer
2016-01-23 Updated to support different Vref voltages
2016-01-25 Change VREF define to capital
2016-01-28 Moved default reference voltage to function prototype so it's known when including the header file
2016-01-28 Fixed if/else logic in computeTemperatureTypeK - changed || to &&
2016-02-21 Fixed vref capitalization
2016-05-16 First cut of 3.3V-capable LTC2499 board
2016-05-16 Change PCB to reflect it's multivoltage, not just 3.3V
2016-05-18 Initial version with I2C level shifter
2016-05-18 Added shorts around level shifter.
2016-12-23 Test fixture
2016-12-23 Add level-shifting version of 1.3
2016-12-26 Moved D1 text. DRC/LVS clean.
2016-12-26 Sent to fab 12/25/2016
2017-02-09 Sketch for the test-ard-ltc2499 design.
2017-08-12 Improved test script
2017-10-02 Support for Wire1 interface on the Due only Add another constructor such that a pointer to the correct wire interface can be passed in if the client wants to explicitly set it.
2017-10-07 Modified test sketch for Due compatibility
2017-12-07 Added a change channel option to the read voltage function
2018-03-04 Updated test procedure
2018-07-17 Arduino Nano design
2018-07-28 Added text and 5V probe point
2018-07-28 XY fie for ard-ltc2499
2018-08-01 Connected test point
2018-08-14 PG for nano version
2019-09-16 Mainline the level-shifted version of v1.3 from the level-shift branch
2021-01-11 Add library.properties files
2021-03-03 New readme to consolidate all the documentation with the project
2021-03-03 Try to fix issue with readme
2021-03-03 Try to fix read again
2021-03-03 Fix issue with eepromWrite doc
2021-03-03 Remove trailing spaces causing weird line breaks
2021-03-03 Add schematic links
2021-03-03 Add link back to store on ARD-LTC2499
2024-05-23 Initial schematic
2024-05-24 Fixed 6654 symbol
2024-05-24 Added test points and individual address pull-ups
2024-05-25 Updated PCB with schematic edits
2024-05-25 Initial placement
2024-05-25 Complete PCB
2024-05-25 Colorized terminal
2024-05-25 Fixed typo
2024-05-25 Fixed terminal block 3D model height
2024-05-25 Adjusted text
2024-05-26 Minor tweaks
2024-05-28 Minor updates to text
2024-05-28 Minor adjustments to metal traces
2024-05-29 Clean up minor DRC warning
2024-05-29 pg v2.0
2024-09-27 Updated for v2
2025-02-01 Initial test board
2025-02-01 Added 5V divider and moved refernce divider to 1.25V
2025-02-23 Updated test script
2025-02-23 Fixed courtyard errors
2025-02-23 Check in tester pg v1.0
2025-02-23 Updated DRC rules
2025-02-23 Fab files for the test jig
2025-02-23 Remove pg 1.0 of tester
2025-03-27 Updated for v2 tester
2025-08-06 Add better models for pin headers to generate step file
2025-08-06 Add step file for v2.0
2025-08-06 Remove old v1.x geda files to clean up repo
2025-08-09 Improved test program
2026-02-13 Switched to arduino-cli

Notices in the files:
kicad/ard-ltc2499-test/ard-ltc2499-test.kicad_pcb:
CC BY-SA ©2025
kicad/ard-ltc2499/ard-ltc2499.kicad_pcb:
CC BY-SA ©2024
